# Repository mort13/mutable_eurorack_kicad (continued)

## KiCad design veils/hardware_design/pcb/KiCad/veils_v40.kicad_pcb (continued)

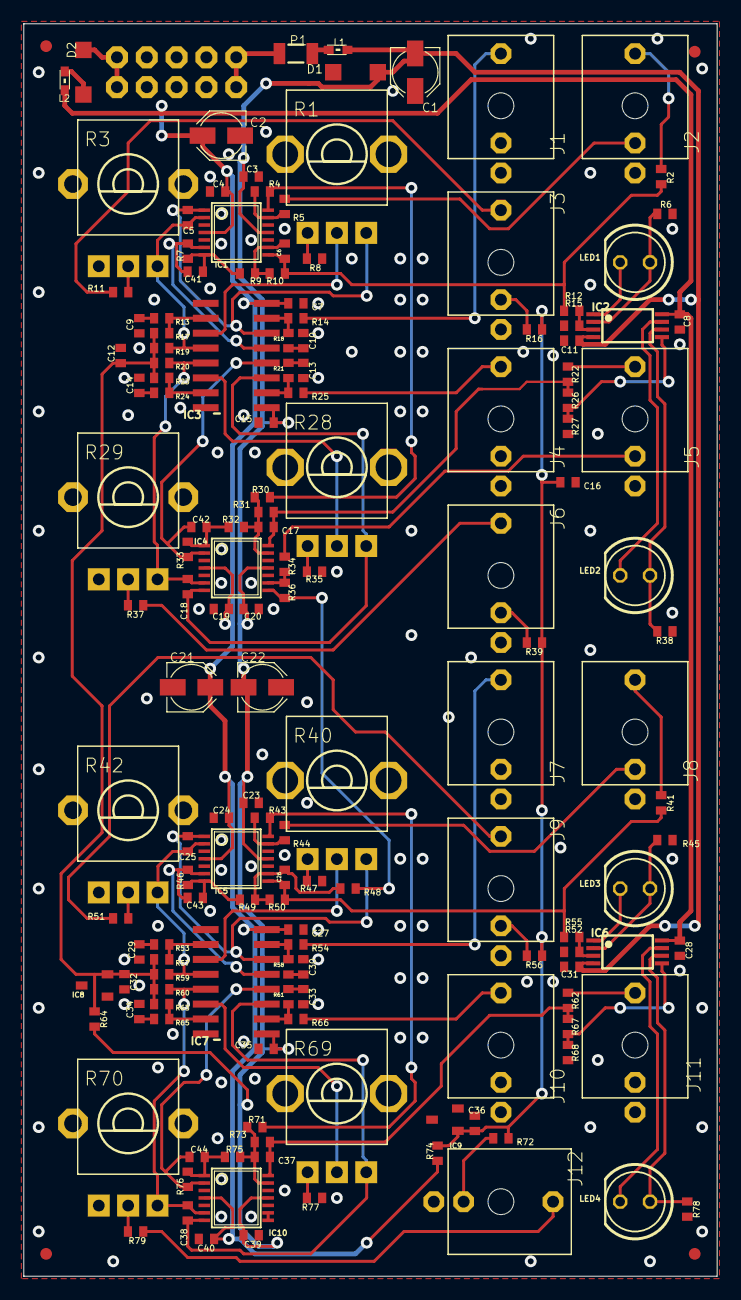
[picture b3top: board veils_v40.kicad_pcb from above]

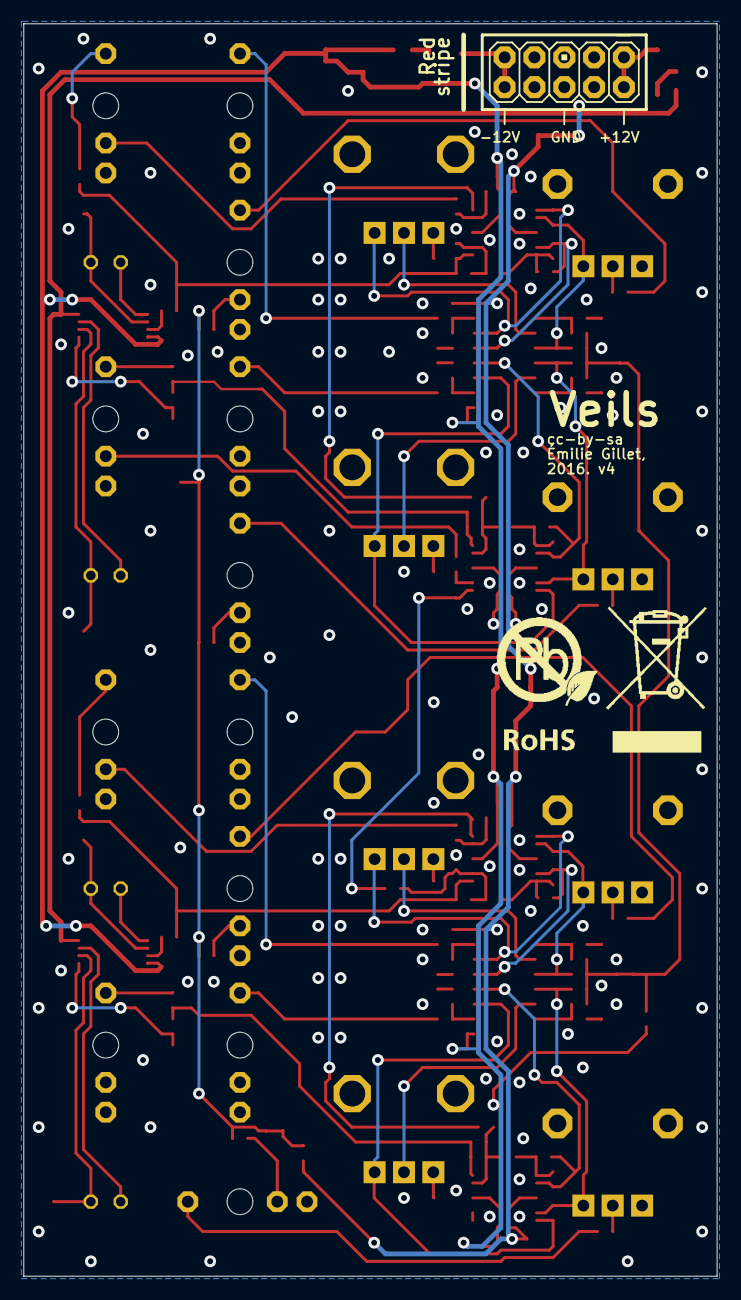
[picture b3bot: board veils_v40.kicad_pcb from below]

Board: 2 copper layers, 59.1 x 106.7 mm, 160 parts (2 on the bottom side), 99 nets.

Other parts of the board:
U$2: ROHS_BIG

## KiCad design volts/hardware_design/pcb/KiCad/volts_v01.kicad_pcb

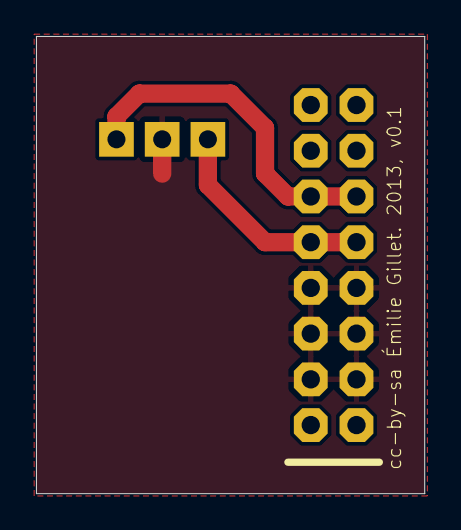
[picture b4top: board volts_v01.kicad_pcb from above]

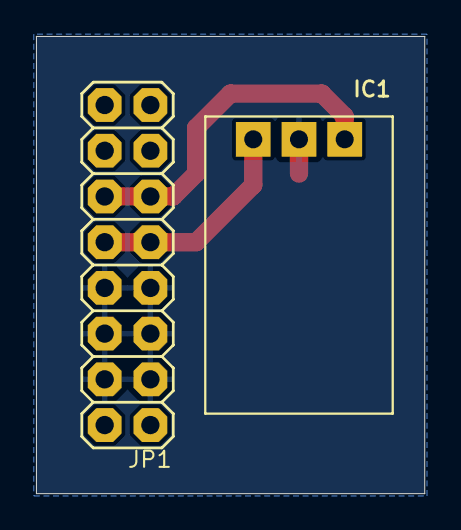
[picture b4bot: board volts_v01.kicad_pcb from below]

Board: 2 copper layers, 21.6 x 25.4 mm, 4 parts (2 on the bottom side), 3 nets.

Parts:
IC1: OKI-78SR-5/1.5-W36-C; OKI78SR
JP1: M08X2; 2X8
U$1: LOGO_5VOLTS
U$2: LOGO_5VOLTS_EDIT

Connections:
GND: IC1.2, JP1.9, JP1.10, JP1.11, JP1.12, JP1.13, JP1.14
unnamed: IC1.1, JP1.7, JP1.8
unnamed: IC1.3, JP1.5, JP1.6

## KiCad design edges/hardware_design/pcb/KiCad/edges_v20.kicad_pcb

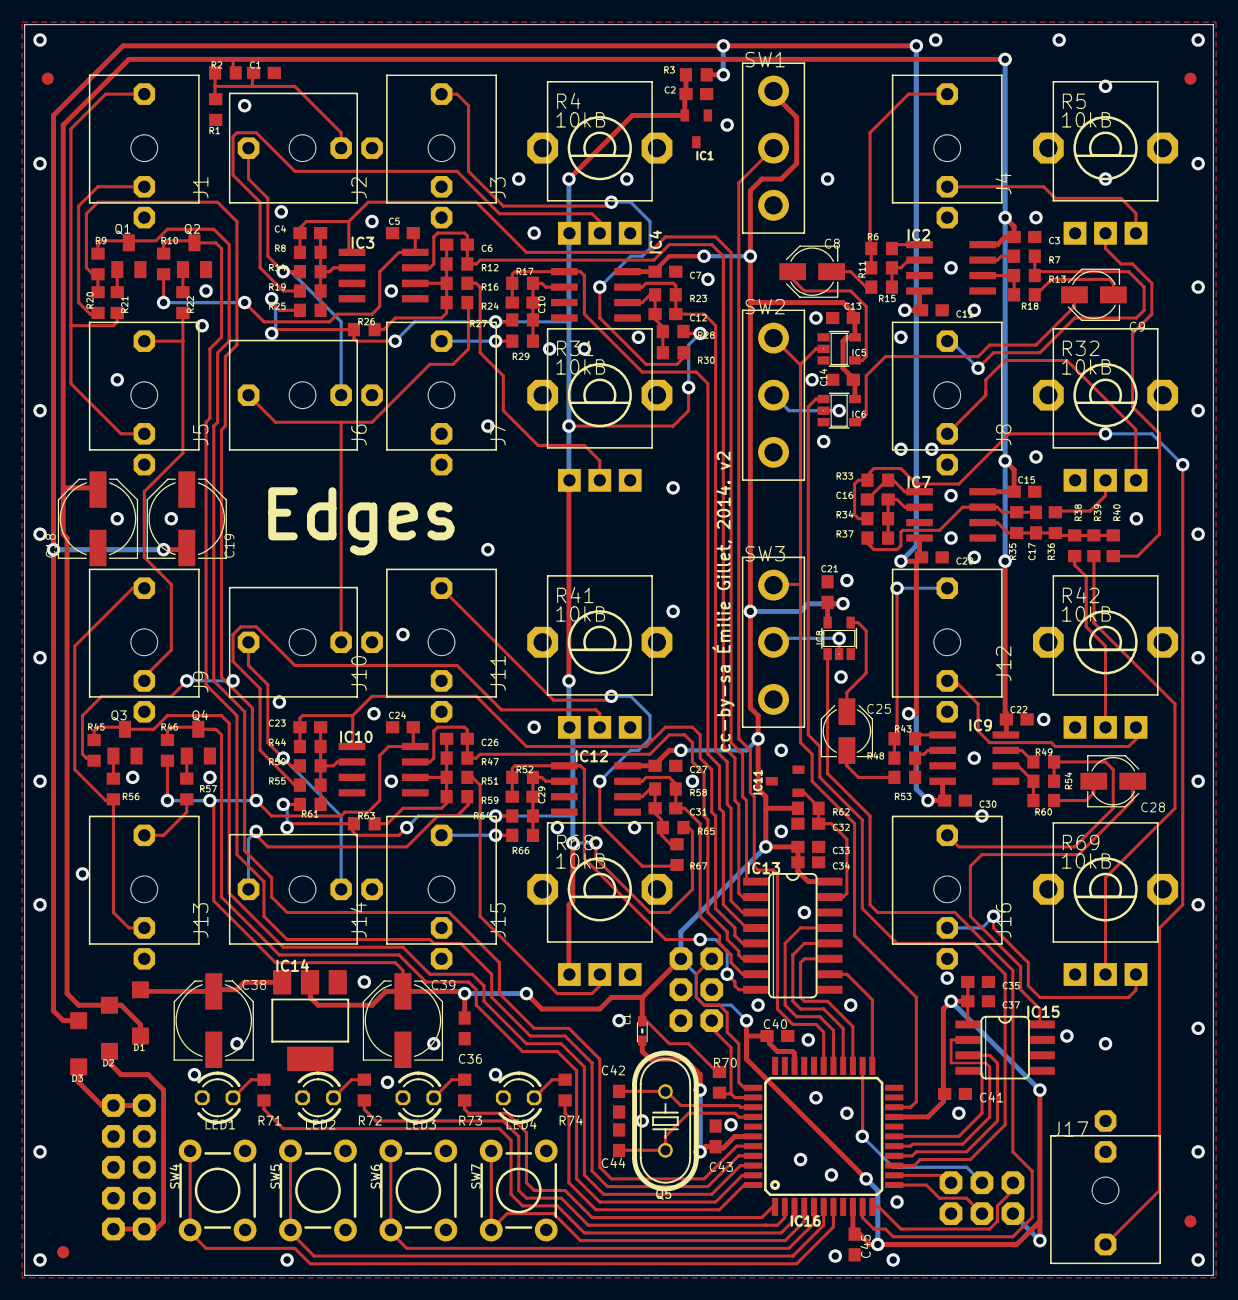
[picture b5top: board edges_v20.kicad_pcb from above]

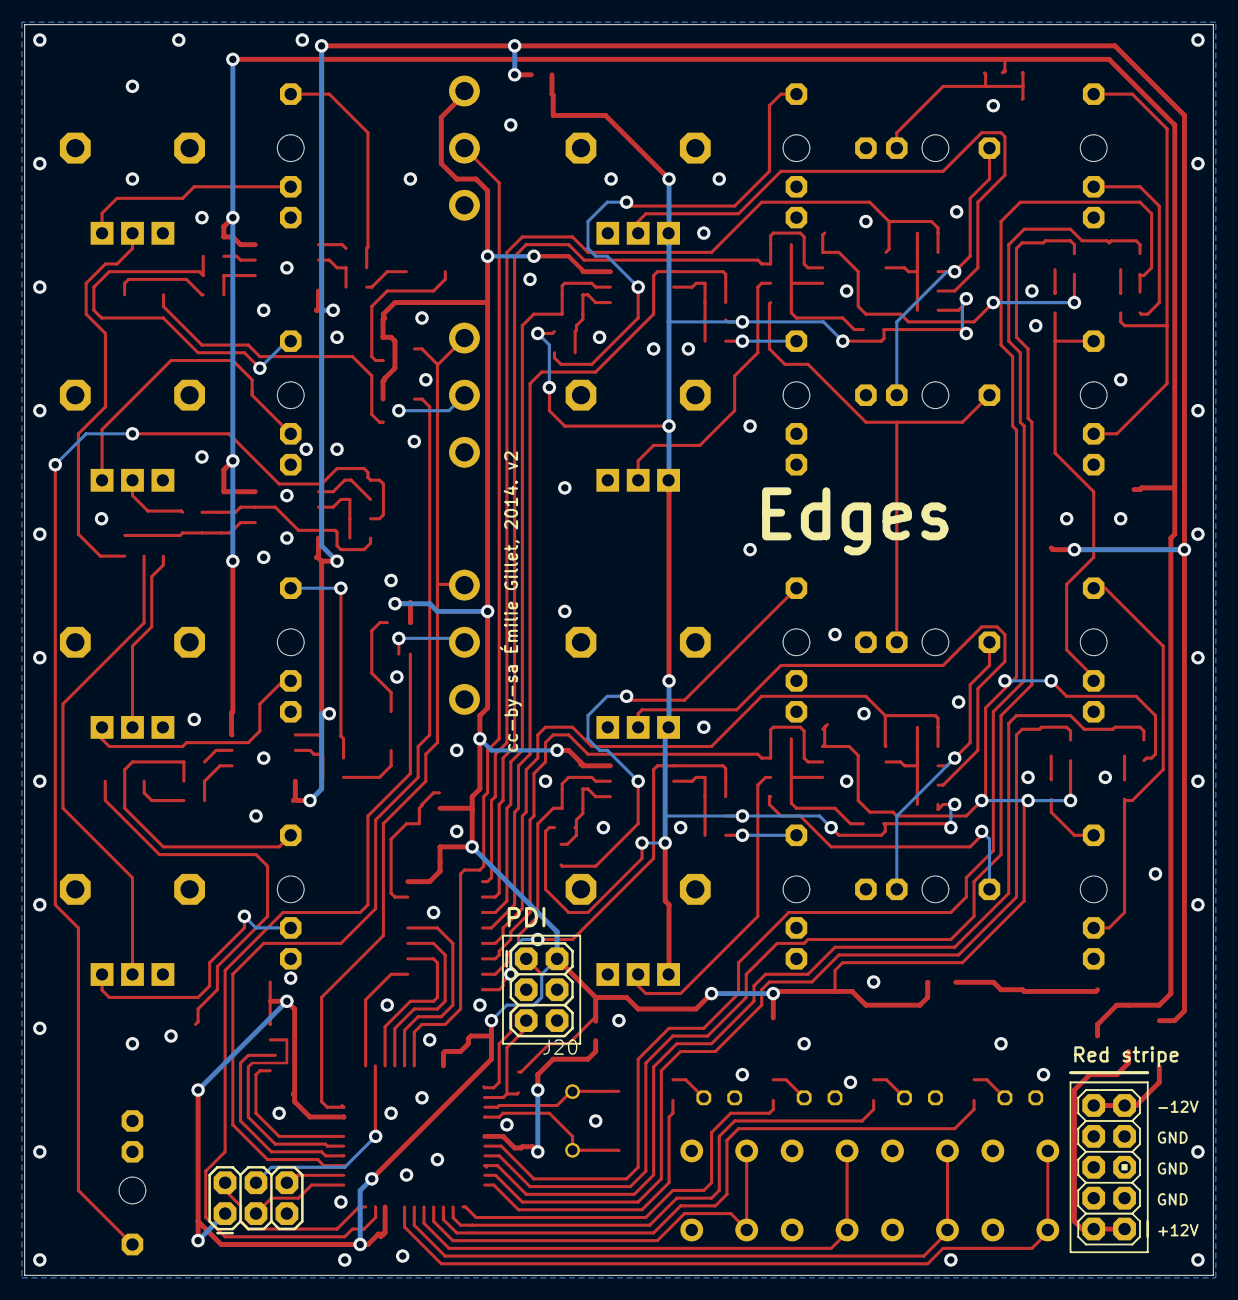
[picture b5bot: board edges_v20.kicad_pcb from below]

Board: 2 copper layers, 97.8 x 102.9 mm, 179 parts (3 on the bottom side), 118 nets.

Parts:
C1, C2, C32: 470n; C0603
C3, C5, C7, C11, C13, C14, C15, C20, C21, C22, C24, C27, C30, C34, C36, C37, C40, C41, C43, C45: 100n; C0603
C4, C6, C10, C12, C23, C26, C29, C31: 100p; C0603
C8, C9, C25, C28: 10u; PANASONIC_B
C16, C17, C42, C44: 18p; C0603
C18, C19, C38, C39: 47u; PANASONIC_D
C33, C35: 1u; C0603
D1, D2, D3: 1N5819HW; SOD123
IC1: LM4040 10V; DBZ_R-PDSO-G3
IC2, IC7, IC9: TL072D; SO08
IC3, IC4, IC10, IC12: MCP6002; SO08
IC5: 74AHC1G125DBV; SOT23-5
IC6, IC8: 74AHC1G86DBV; SOT23-5
IC11: LM4040B25; DBZ_R-PDSO-G3
IC13: MCP3208; SO16
IC14: LM1117-3.3; SOT223
IC15: MCP4822; SO08
IC16: ATXMEGA32A4U-AU; TQFP44
J1, J2, J3, J4, J5, J6, J7, J8, J9, J10, J11, J12, J13, J14, J15, J16, J17: PJ301_THONKICONN6; WQP_PJ_301M6
J18, J20: 2X3
J19: M05X2PTH; AVR_ICSP
JP1, JP2, JP3, JP4: FIDUCIAL1X2; FIDUCIAL-1X2
L1: 0603
LED1, LED2, LED3, LED4: LED3MM
Q1, Q2, Q3, Q4: MMBT3904; SOT23-BEC
Q5: 8MHz; HC49U70
R1: 2k; R0603
R2, R9, R10, R15, R18, R45, R46, R53, R60: 10k; R0603
R3: 300; R0603
R4, R5, R31, R32, R41, R42, R68, R69: 10kB; ALPS_POT_VERTICAL_PS
R6, R7, R20, R33, R43, R49, R62: 1k; R0603
R8, R12, R17, R23, R44, R47, R52, R58: 24.9k; R0603
R11, R13, R35, R48: 33k; R0603
R14, R21, R22, R24, R29, R30, R34, R36, R37, R38, R40, R50, R56, R57, R59, R66, R67: 100k; R0603
R16, R19, R25, R26, R27, R28, R51, R55, R61, R63, R64, R65: 200k; R0603
R39, R70: 39k; R0603
R54: 82k; R0603
R71, R72, R73, R74: 100; R0603
SW1, SW2, SW3: ES_100SP1T6B11M2QEH_SMALL
SW4, SW5, SW6, SW7: TACTILE-PTH

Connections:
+3V3: C5.1, C7.1, C13.1, C14.1, C21.1, C24.1, C27.1, C33.1, C34.1, C35.1, C36.1, C37.1, C39.+, C40.1, C41.1, C45.1, IC3.8, IC4.8, IC5.5, IC6.5, IC8.5, IC10.8, IC12.8, IC13.16, IC14.2, IC15.1, IC16.9, IC16.19, IC16.31, J18.1, J20.2, L1.1, R9.2, R10.2, R20.1, R45.2, R46.2, R62.1, R70.2, SW1.O
ADC_MISO: IC13.12, IC16.26
ADC_MOSI: IC13.11, IC16.25
ADC_SCK: IC13.13, IC16.27
ADC_SS: IC13.10, IC16.23
AREF: C32.1, IC11.1, IC13.15, R62.2
AREF_-10: C2.1, IC1.2, R3.2, R4.P$3, R25.1, R26.1, R27.1, R28.1, R31.P$3, R41.P$3, R61.1, R63.1, R64.1, R65.1, R68.P$3
CH1: C4.2, IC3.1, IC13.1, R8.2
CH2: C6.2, IC3.7, IC13.2, R12.2
CH3: C23.2, IC10.1, IC13.5, R44.2
CH4: C26.2, IC10.7, IC13.6, R47.2
CH5: C12.2, IC4.7, IC13.3, R23.2
CH6: C10.2, IC4.1, IC13.4, R17.2
CH7: C31.2, IC12.7, IC13.7, R58.2
CH8: C29.2, IC12.1, IC13.8, R52.2
CHANNEL1: C8.+, IC5.4
CHANNEL1_BUFFERED: J4.P3, R6.2, R11.2
CHANNEL1_RETURN: R5.P$2, R40.1
CHANNEL2: C9.+, IC6.4
CHANNEL2_BUFFERED: J8.P3, R7.2, R13.2
CHANNEL2_RETURN: R32.P$2, R36.1
CHANNEL3: C25.+, IC8.4
CHANNEL3_BUFFERED: J12.P3, R43.2, R48.2
CHANNEL3_RETURN: R38.1, R42.P$2
CHANNEL4: C28.+, IC15.8
CHANNEL4_BUFFERED: J16.P3, R49.2, R54.2
CHANNEL4_RETURN: R39.1, R69.P$2
COARSE1: R4.P$2, R19.1
COARSE2: R16.1, R31.P$2
COARSE3: R41.P$2, R55.1
COARSE4: R51.1, R68.P$2
CV1: J2.P3, J6.P2, R14.1
CV2: J6.P3, J10.P2, R24.1
CV3: J10.P3, J14.P2, R50.1
CV4: J14.P3, R59.1
DAC_MOSI: IC15.4, IC16.17
DAC_SCK: IC15.3, IC16.15
DAC_SS: IC15.2, IC16.16
FM1: J3.P3, R30.1
FM2: J7.P3, R29.1
FM3: J11.P3, R67.1
FM4: J15.P3, R66.1
GATE1: IC16.40, Q1.C, R9.1
GATE1_IN: J1.P3, J5.P2, R21.2
GATE1_LED: LED4.A, R74.2
GATE2: IC16.41, Q2.C, R10.1
GATE2_IN: J5.P3, J9.P2, R22.2
GATE2_LED: LED3.A, R73.2
GATE3: IC16.42, Q3.C, R45.1
GATE3_IN: J9.P3, J13.P2, R56.2
GATE3_LED: LED2.A, R72.2
GATE4: IC16.43, Q4.C, R46.1
GATE4_IN: J13.P3, R57.2
GATE4_LED: LED1.A, R71.2
GND: C1.2, C2.2, C3.2, C5.2, C7.2, C11.1, C13.2, C14.2, C15.2, C18.-, C19.+, C20.1, C21.2, C22.2, C24.2, C27.2, C30.1, C32.2, C33.2, C34.2, C35.2, C36.2, C37.2, C38.-, C39.-, C40.2, C41.2, C42.1, C43.2, C44.1, C45.2, IC1.1, IC2.3, IC2.5, IC3.3, IC3.4, IC3.5, IC4.3, IC4.4, IC4.5, IC5.1, IC5.3, IC6.3, IC7.3, IC7.5, IC8.3, IC9.3, IC9.5, IC10.3, IC10.4, IC10.5, IC11.2, IC12.3, IC12.4, IC12.5, IC13.9, IC13.14, IC14.1, IC15.5, IC15.7, IC16.8, IC16.18, IC16.30, IC16.38, J1.P1, J2.P1, J3.P1, J4.P1, J5.P1, J6.P1, J7.P1, J8.P1, J9.P1, J10.P1, J11.P1, J12.P1, J13.P1, J14.P1, J15.P1, J16.P1, J17.P1, J18.5, J19.3, J19.4, J19.5, J19.6, J19.7, J19.8, J20.6, LED1.K, LED2.K, LED3.K, LED4.K, Q1.E, Q2.E, Q3.E, Q4.E, R1.1, R4.P$1, R5.P$3, R31.P$1, R32.P$3, R41.P$1, R42.P$3, R68.P$1, R69.P$3, SW1.S, SW2.O, SW3.O, SW4.3, SW4.4, SW5.3, SW5.4, SW6.3, SW6.4, SW7.3, SW7.4
MIDI_IN: IC16.12, J18.3
MIX: J17.P3, R33.2, R34.2
unnamed: Q1.B, R21.1
unnamed: Q2.B, R22.1
unnamed: Q3.B, R56.1
unnamed: J8.P2, R32.P$1
unnamed: IC16.44, R74.1
unnamed: IC16.1, R73.1
unnamed: IC16.2, R72.1
unnamed: IC16.3, R71.1
unnamed: C23.1, IC10.2, R44.1, R50.2, R55.2, R61.2
unnamed: C10.1, IC4.2, R17.1, R27.2, R29.2
unnamed: J1.P2, R20.2
unnamed: C26.1, IC10.6, R47.1, R51.2, R59.2, R63.2
unnamed: C31.1, IC12.6, R58.1, R65.2, R67.2
unnamed: C29.1, IC12.2, R52.1, R64.2, R66.2
unnamed: IC6.1, IC16.14
unnamed: C8.-, R15.1
unnamed: IC8.2, SW3.P
unnamed: IC2.2, R11.1, R15.2
unnamed: IC2.1, R6.1
unnamed: IC6.2, SW2.P
unnamed: C9.-, R18.1
unnamed: IC2.6, R13.1, R18.2
unnamed: IC2.7, R7.1
unnamed: C25.-, R53.1
unnamed: C12.1, IC4.6, R23.1, R28.2, R30.2
unnamed: IC9.2, R48.1, R53.2
unnamed: IC9.1, R43.1
unnamed: C28.-, R60.1
unnamed: IC9.6, R54.1, R60.2
unnamed: IC9.7, R49.1
unnamed: C17.1, IC7.6, R35.1, R36.2, R38.2, R39.2, R40.2
unnamed: C16.1, IC7.2, R34.1, R37.2
unnamed: C16.2, IC7.1, R33.1
unnamed: C38.+, D1.C, IC14.3
unnamed: C43.1, IC16.39, L1.2
unnamed: J4.P2, R5.P$1
unnamed: IC8.1, IC16.10
unnamed: C17.2, IC7.7, R35.2, R37.1
unnamed: J12.P2, R42.P$1
unnamed: J16.P2, R69.P$1
unnamed: C6.1, IC3.6, R12.1, R16.2, R24.2, R26.2
unnamed: C1.1, J2.P2, R1.2, R2.1
unnamed: D2.A, J19.1, J19.2
unnamed: IC5.2, IC16.20, SW2.S, SW3.S
unnamed: D3.C, J19.9, J19.10
unnamed: C4.1, IC3.2, R8.1, R14.2, R19.2, R25.2
unnamed: C44.2, IC16.37, Q5.1
unnamed: C42.2, IC16.36, Q5.2
unnamed: Q4.B, R57.1
NES_TRIANGLE_CLK: IC16.24, J18.4
PDICLK: IC16.35, J20.5, R70.1
PDIDATA: IC16.34, J20.1
SW1: IC16.4, SW7.1, SW7.2
SW2: IC16.5, SW6.1, SW6.2
SW3: IC16.6, SW5.1, SW5.2
SW4: IC16.7, SW4.1, SW4.2
SW_MIDI_LEARN: IC16.11, J18.2
SW_MIDI_MODE: IC16.13, J18.6
SYNC_SWITCH: IC16.28, SW1.P
VCC: C3.1, C15.1, C18.+, C22.1, D1.A, D2.C, IC2.8, IC7.8, IC9.8, R2.2
VEE: C11.2, C19.-, C20.2, C30.2, D3.A, IC2.4, IC7.4, IC9.4, R3.1

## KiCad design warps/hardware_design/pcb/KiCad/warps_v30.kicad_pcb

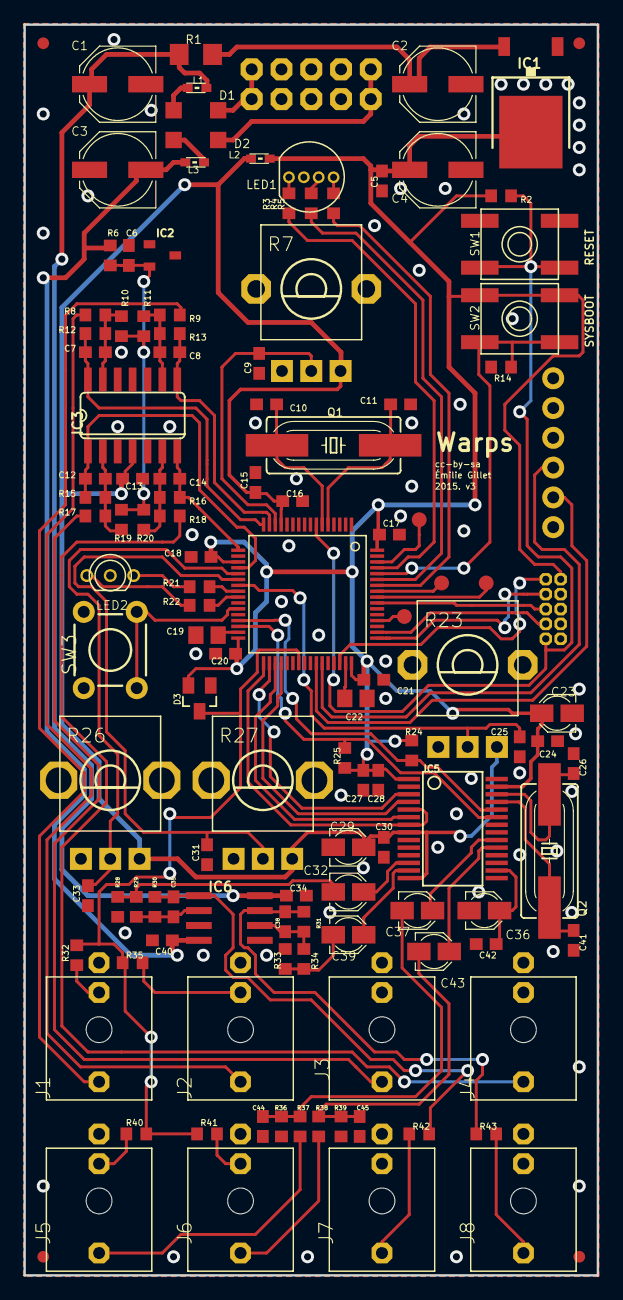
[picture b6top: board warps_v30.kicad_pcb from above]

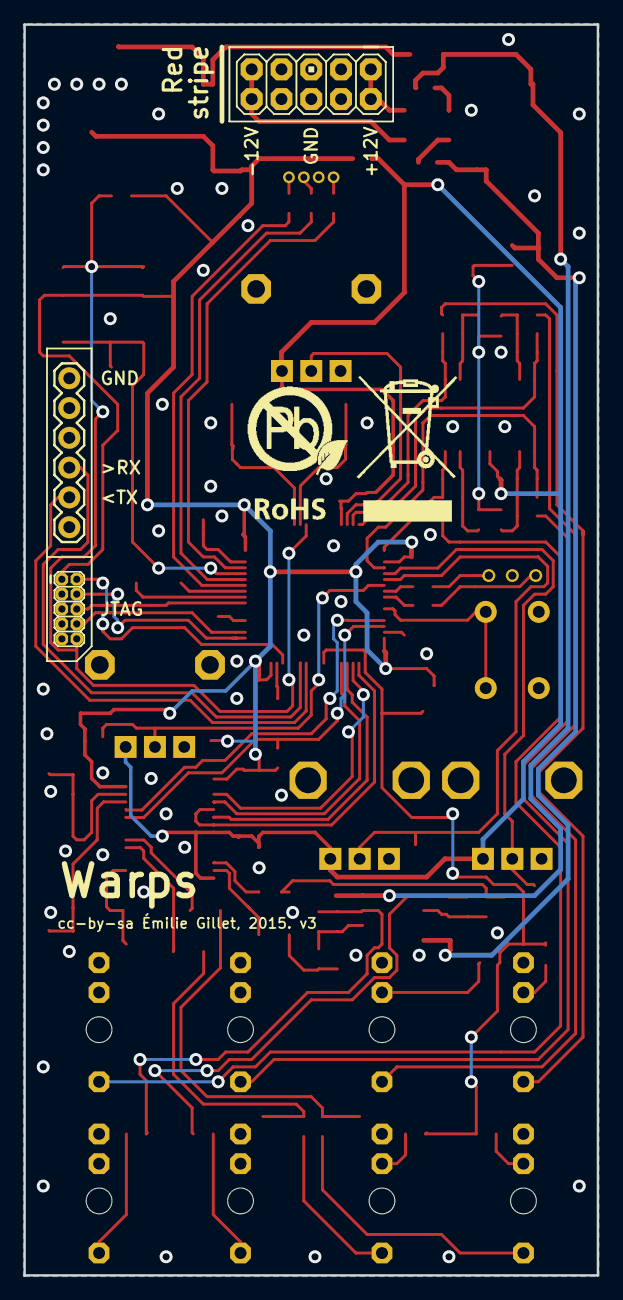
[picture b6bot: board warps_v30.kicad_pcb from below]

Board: 2 copper layers, 48.9 x 106.7 mm, 127 parts (4 on the bottom side), 84 nets.

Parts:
C1, C2, C3, C4: 47u; PANASONIC_D
C5, C6, C9, C13, C16, C17, C18, C20, C21, C24, C25, C28, C30, C31, C33, C34, C40, C42: 100n; C0603
C7, C8, C12, C14: 4.7n; C0603
C10, C11, C26, C35, C38, C41: 18p; C0603
C15, C27: 1u; C0603
C19, C22: 2.2u; C0805
C23, C29, C32, C36, C37, C39, C43: 10u; PANASONIC_A
C44, C45: 220p; C0603
D1, D2: 1N5819HW; SOD123
D3: BAT54S; SOT23
F1, F2, F3, F4: FIDUCIAL1X2; FIDUCIAL-1X2
IC1: LM1117-3.3; TO252
IC2: LM4040B10; DBZ_R-PDSO-G3
IC3: MCP6004; SO14
IC4: STM32F405RGT6; TQFP-10X10-64
IC5: WM8731; SSOP28
IC6: TL072; SO08
J1, J2, J3, J4, J5, J6, J7, J8: PJ301_THONKICONN6; WQP_PJ_301M6
JP1: M05X2MINIJTAG; 2X5-1.27
JP2: 1X06
JP3: M05X2PTH; AVR_ICSP
L1, L2, L3: 0603
LED1: WP154A4SUREQBFZG; LED-TRICOLOR-THROUGHHOLE
LED2: WP115VEGW; LED-BICOLOR-THROUGHHOLE
Q1: 8MHz; HC49UP
Q2: 12.288MHz; HC49UP
R1: 4.7; R1206
R2, R14: 10k; R0603
R3, R4, R5: 100; R0603
R6: 4.7k; R0603
R7, R23: 10kB; ALPS_POT_VERTICAL_PS
R8, R9, R17, R18: 100k; R0603
R10, R11: 120k; R0603
R12, R13, R37, R38: 36k; R0603
R15, R16: 33k; R0603
R19, R20, R32, R35: 200k; R0603
R21, R22: 180; R0603
R24, R25: 2.2k; R0603
R26, R27: 10kB; ALPS_POT_VERTICAL
R28, R30, R31, R33: 47k; R0603
R29, R34, R36, R39: 6.8k; R0603
R40, R41: DNP; R0603
R42, R43: 1.0k; R0603
SW1, SW2: EVQ-Q2
SW3: TACTILE-PTH
TP1, TP2, TP3, TP4: TEST-POINT3X5; PAD.03X.05
U$2: ROHS_BIG

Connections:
+3V3: C4.+, C5.1, C17.1, C18.1, C20.1, C21.1, C23.+, C24.1, C27.1, C28.1, D3.2, IC1.3, IC4.19, IC4.32, IC4.48, IC4.64, IC5.1, IC5.27, JP1.1, L2.1, R2.2, R24.2, R25.2, SW2.B, SW2.B'
+3V3_A: C13.1, C15.1, C16.1, C29.+, C30.1, IC3.4, IC4.13, IC5.8, IC5.14, L2.2, R7.P$1, R23.P$1, R26.P$1, R27.P$1
ALGORITHM_CV: C12.2, IC3.1, IC4.20, R15.1
ALGORITHM_POT: C9.1, IC4.14, R7.P$2
AREF_-10: C6.1, IC2.2, R6.2, R10.2, R11.2, R19.2, R20.2
AUX_OUT: C39.+, IC5.13
BOOT_FLASH: IC4.60, R14.2, SW2.A, SW2.A'
GND: C1.-, C2.-, C3.+, C4.-, C5.2, C6.2, C9.2, C10.1, C11.1, C13.2, C15.2, C16.2, C17.2, C18.2, C19.2, C20.2, C21.2, C22.2, C23.-, C24.2, C25.2, C26.1, C27.2, C28.2, C29.-, C30.2, C31.2, C33.2, C34.2, C36.-, C40.1, C41.1, C42.2, C44.2, C45.2, D3.1, IC1.1, IC2.1, IC3.3, IC3.5, IC3.10, IC3.11, IC3.12, IC4.12, IC4.18, IC4.26, IC4.28, IC4.63, IC5.11, IC5.15, IC5.21, IC5.22, IC5.28, IC6.3, IC6.5, J1.P1, J2.P1, J3.P1, J4.P1, J5.P1, J6.P1, J7.P1, J8.P1, JP1.3, JP1.5, JP1.9, JP2.1, JP3.3, JP3.4, JP3.5, JP3.6, JP3.7, JP3.8, LED1.GND, LED2.2, R7.P$3, R14.1, R23.P$3, R26.P$3, R27.P$3, R28.1, R33.1, R36.1, R39.1, SW1.A, SW1.A', SW3.1, SW3.2
I2C_SCL: IC4.29, IC5.24, R24.1
I2C_SDA: IC4.30, IC5.23, R25.1
I2S_LRCK: IC4.33, IC5.5, IC5.7
I2S_SCK: IC4.34, IC5.3
I2S_SIN: IC4.35, IC5.6
I2S_SOUT: IC4.36, IC5.4
IN_1: C37.+, IC5.20
IN_2: C43.+, IC5.19
JTCK: IC4.49, JP1.4
JTDI: IC4.50, JP1.8
JTDO: IC4.55, JP1.6
JTMS: IC4.46, JP1.2
LED_B: IC4.59, R4.1
LED_CARRIER_G: IC4.25, R22.1
LED_CARRIER_R: IC4.24, R21.1
LED_G: IC4.58, R5.1
LED_R: IC4.61, R3.1
LEVEL_1_CV: C8.2, IC3.8, IC4.15, R13.1
LEVEL_1_POT: C33.1, IC4.21, R26.P$2
LEVEL_2_CV: C7.2, IC3.14, IC4.16, R12.1
LEVEL_2_POT: C31.1, IC4.22, R27.P$2
MOD_OUT: C32.+, IC5.12
unnamed: J1.P3, R9.2
unnamed: C8.1, IC3.9, R9.1, R11.1, R13.2
unnamed: LED2.3, R21.2
unnamed: J2.P3, R8.2
unnamed: C7.1, IC3.13, R8.1, R10.1, R12.2
unnamed: J4.P3, R18.2
unnamed: C11.2, IC4.5, Q1.2
unnamed: C10.2, IC4.6, Q1.1
unnamed: J1.P2, R32.2
unnamed: J3.P3, R17.2
unnamed: C12.1, IC3.2, R15.2, R17.1, R19.1
unnamed: J2.P2, R35.2
unnamed: C22.1, IC4.47
unnamed: LED2.1, R22.2
unnamed: C14.1, IC3.6, R16.2, R18.1, R20.1
unnamed: C2.+, IC1.2, R1.1
unnamed: C36.+, C42.1, IC5.16
unnamed: C37.-, C44.1, R36.2, R37.1
unnamed: C19.1, IC4.31
unnamed: J6.P3, R38.2
unnamed: J5.P3, R37.2
unnamed: C43.-, C45.1, R38.1, R39.2
unnamed: C39.-, R33.2, R34.2
unnamed: IC4.56, TP3.P$1
unnamed: C38.1, IC6.6, R31.2, R34.1
unnamed: IC4.57, TP2.P$1
unnamed: IC4.52, TP4.P$1
unnamed: C38.2, IC6.7, R31.1, R43.2
unnamed: J8.P3, R43.1
unnamed: IC4.62, TP1.P$1
unnamed: C32.-, R28.2, R29.2
unnamed: C35.1, IC6.2, R29.1, R30.2
unnamed: C35.2, IC6.1, R30.1, R42.2
unnamed: J7.P3, R42.1
unnamed: LED1.RED, R3.2
unnamed: LED1.BLU, R4.2
unnamed: LED1.GRN, R5.2
unnamed: J6.P2, R41.1
unnamed: J5.P2, R40.1
unnamed: C41.2, IC5.25, Q2.2
unnamed: C26.2, IC5.26, Q2.1
unnamed: D1.C, L1.2
unnamed: D2.A, L3.2
unnamed: D1.A, JP3.1, JP3.2
unnamed: D2.C, JP3.9, JP3.10
NORMALIZATION_PROBE: D3.3, IC4.39, R32.1, R35.1, R40.2, R41.2
PARAMETER_CV: C14.2, IC3.7, IC4.17, R16.1
PARAMETER_POT: C25.1, IC4.23, R23.P$2
RESET: IC4.7, JP1.10, R2.1, SW1.B, SW1.B'
RX: IC4.43, JP2.4
SW_CARRIER: IC4.27, SW3.3, SW3.4
TX: IC4.42, JP2.5
VCC: C1.+, C34.1, IC6.8, L1.1, R1.2
VEE: C3.-, C40.2, IC6.4, L3.1, R6.1

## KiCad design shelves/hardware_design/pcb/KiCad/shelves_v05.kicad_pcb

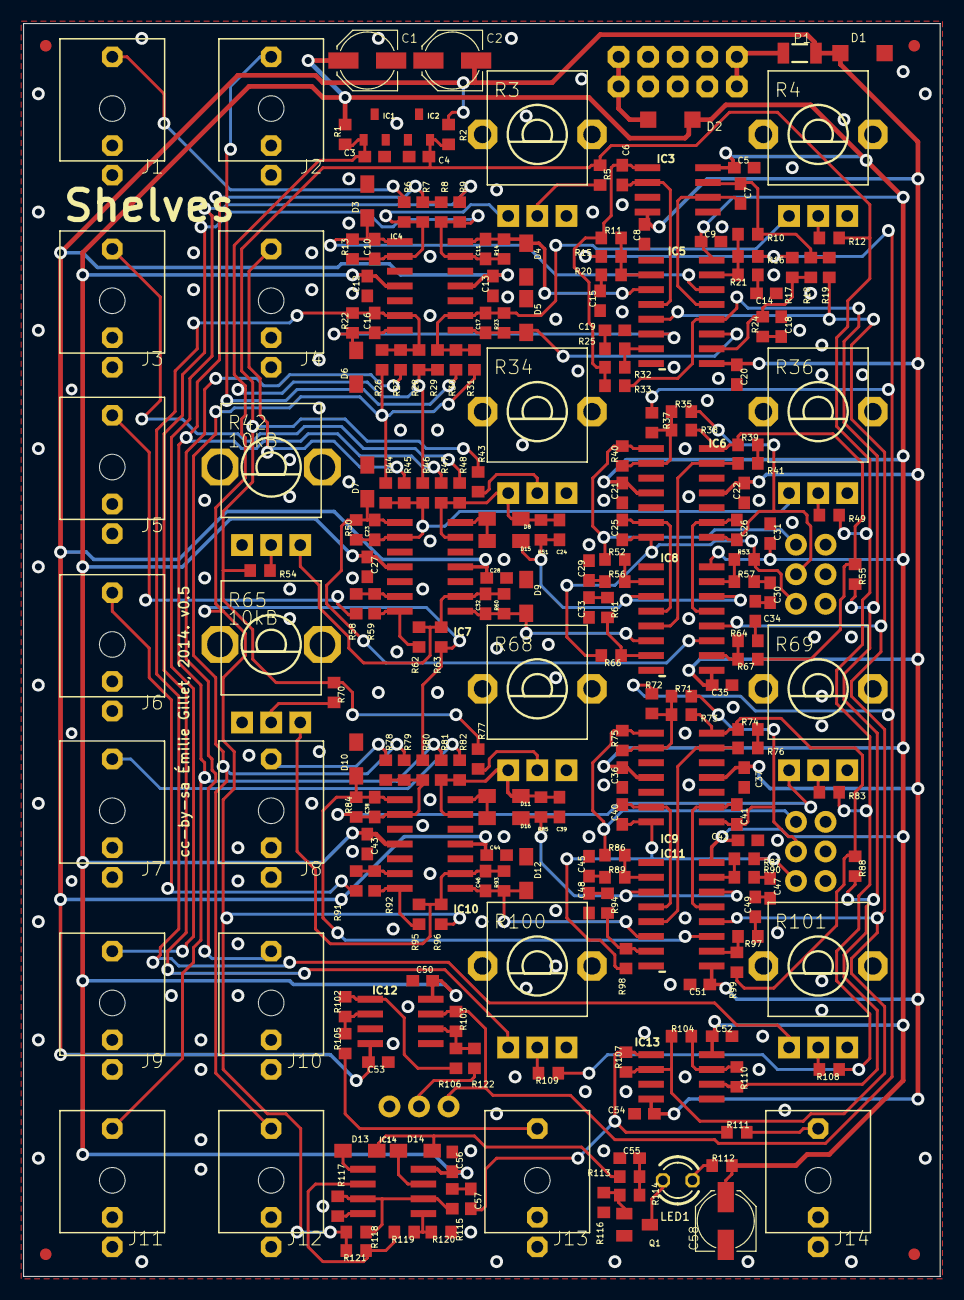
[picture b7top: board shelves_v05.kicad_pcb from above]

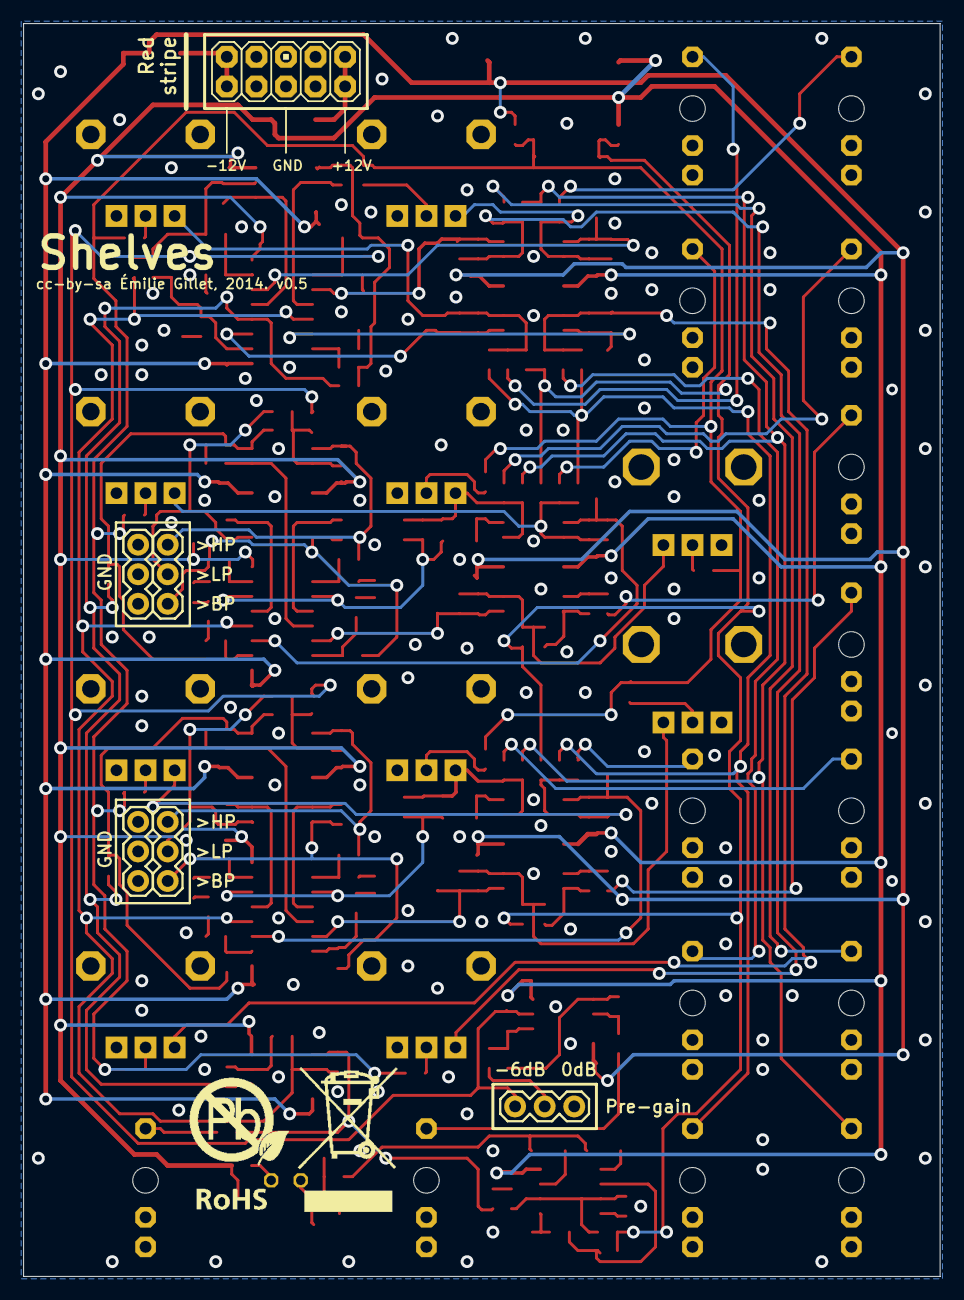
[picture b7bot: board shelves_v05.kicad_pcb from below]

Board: 2 copper layers, 78.7 x 107.6 mm, 238 parts (7 on the bottom side), 123 nets.

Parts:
C1, C2, C58: 22u; PANASONIC_C
C3, C4, C5, C8, C9, C12, C13, C20, C21, C22, C27, C28, C31, C35, C36, C37, C42, C43, C44, C50, C51, C52, C53, C54, C55, C56, C57: 100n; C0603
C6, C7, C25, C26, C40, C41: 68p; C0603
C10, C11, C14, C15, C16, C17, C18, C19, C23, C24, C29, C30, C32, C33, C34, C38, C39, C45, C46, C47, C48, C49: 560p; C0603
D1, D2: 1N5819HW; SOD123
D3, D4, D5, D6, D7, D8, D9, D10, D11, D12, D13, D14, D15, D16: 1N4148; SOD323-W
IC1, IC2: LM4040B10; DBZ_R-PDSO-G3
IC3, IC12, IC13, IC14: TL072D; SO08
IC4, IC6, IC7, IC9, IC10: TL074D; SO14
IC5, IC8, IC11: V2164SZ; SOIC16N
J1, J2, J3, J4, J5, J6, J7, J8, J9, J10, J11, J12, J13, J14: PJ301_THONKICONN6; WQP_PJ_301M6
JP1, JP2, JP3, JP4: FIDUCIAL1X2; FIDUCIAL-1X2
JP5, JP6, JP7, JP12, JP13: 1X03
JP11: M05X2PTH; AVR_ICSP
LED1: WP-710A10GD; LED3MM
P1: PTCSMD; PTC-1206
Q1: MMBT3904; SOT23-BEC
R1: 3.3k; R0603
R2, R111, R112: 1.0k; R0603
R3, R4, R34, R36, R68, R69, R100, R101: 10kB; ALPS_POT_VERTICAL_PS
R5, R6, R7, R8, R9, R10, R11, R12, R15, R16, R17, R18, R19, R32, R33, R35, R37, R38, R39, R40, R41, R43, R47, R48, R49, R52, R53, R55, R58, R59, R66, R67, R71, R72, R73, R74, R75, R76, R77, R81, R82, R83, R86, R87, R88, R91, R92, R98, R99, R102, R103, R104, R105, R108, R109, R110, R114, R115, R117, R118, R120, R121, R122: 100k; R0603
R13, R14, R51, R85: 18k; R0603
R20, R21, R24, R25, R56, R57, R61, R64, R89, R90, R94, R97: 510; R0603
R22, R23, R50, R84, R113: 12k; R0603
R26, R27, R30, R31, R44, R45, R78, R79: 120k; R0603
R28, R29, R46, R54, R70, R80, R106, R107: 200k; R0603
R42, R65: 10kB; ALPS_POT_VERTICAL
R60, R93, R116: 22k; R0603
R62, R95: 150k; R0603
R63, R96: 1.5M; R0603
R119: 220k; R0603
U$2: ROHS_BIG

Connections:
AREF_+10: C3.1, IC1.1, R1.2, R28.1, R29.1, R46.1, R63.1, R80.1, R96.1, R118.2, R121.2
AREF_-10: C4.1, IC2.2, R2.2, R5.1, R12.1, R43.1, R49.1, R54.1, R70.1, R77.1, R83.1, R108.1, R109.1
BP_1: C40.2, IC9.7, JP13.1, R87.1, R98.1
BP_2: C25.2, IC6.7, JP5.1, R53.1, R66.1
F_GLOBAL: J11.P3, R7.1, R8.1, R47.1, R81.1
GAIN_GLOBAL: J12.P3, R26.1, R31.1, R44.1, R79.1
GND: C1.-, C2.+, C3.2, C4.2, C5.2, C8.1, C9.2, C12.2, C13.1, C14.2, C15.2, C18.2, C19.2, C20.1, C21.2, C22.1, C27.2, C28.1, C29.2, C30.2, C31.2, C33.2, C34.2, C35.1, C36.2, C37.1, C42.2, C43.2, C44.1, C45.2, C47.2, C48.2, C49.2, C50.2, C51.1, C52.2, C53.1, C54.1, C55.2, C56.2, C58.-, D1.C, D3.A, D4.A, D5.A, D6.A, D7.A, D9.A, D10.A, D12.A, IC1.2, IC2.1, IC3.3, IC3.5, IC4.3, IC4.5, IC4.10, IC4.12, IC5.8, IC6.3, IC6.5, IC6.10, IC6.12, IC7.3, IC7.5, IC7.10, IC7.12, IC8.8, IC9.3, IC9.5, IC9.10, IC9.12, IC10.3, IC10.5, IC10.10, IC10.12, IC11.8, IC12.3, IC12.5, IC13.3, IC13.5, IC14.4, J1.P1, J2.P1, J3.P1, J4.P1, J5.P1, J6.P1, J7.P1, J8.P1, J9.P1, J10.P1, J11.P1, J12.P1, J13.P1, J14.P1, JP6.1, JP6.2, JP6.3, JP7.1, JP7.2, JP7.3, JP11.3, JP11.4, JP11.5, JP11.6, JP11.7, JP11.8, Q1.E, R3.P$1, R4.P$1, R34.P$1, R36.P$1, R42.P$3, R65.P$3, R68.P$1, R69.P$1, R100.P$1, R101.P$1, R116.1, R117.1, R120.1
HP_1: IC9.1, JP13.3, R75.2, R86.1
HP_2: IC6.1, JP5.3, R40.2, R52.1
IN: IC12.7, JP12.3, R15.1, R16.1, R17.1, R37.1, R72.1, R103.2
IN_INV: IC12.1, R102.2, R106.1
IN_INV1: IC13.7, R104.1, R110.2
J_HF_CV: J2.P3, R30.1
J_HF_F: J1.P3, R6.1
J_IN: J13.P3, R105.1
J_LF_CV: J10.P3, R27.1
J_LF_F: J9.P3, R9.1
LP: C6.2, IC3.1, R11.2, R32.1, R33.1
LP1: C7.2, IC3.7, R10.2, R18.1, R19.1
MID1_F1: C24.1, D15.C, IC8.3, IC8.14, R51.2
MID1_F2: C39.1, D16.C, IC11.3, IC11.14, R85.2
MINUS_BUS: IC5.5, IC8.12, IC11.12, IC13.2, R19.2, R104.2, R107.1
unnamed: IC5.2, R11.1, R15.2, R20.2
unnamed: C19.1, R25.1
unnamed: C11.1, D4.C, IC4.14, IC5.3, R14.2
unnamed: C6.1, IC3.2, IC5.4
unnamed: C14.1, R21.1
unnamed: JP12.2, R122.2
unnamed: C16.1, D6.C, IC4.7, IC5.6, R22.2
unnamed: D11.C, D16.A, IC10.14
unnamed: IC12.2, R102.1, R105.2
unnamed: C15.1, R20.1
unnamed: IC10.7, R92.2, R95.1
unnamed: R100.P$2, R109.2
unnamed: C16.2, IC4.6, R22.1, R26.2, R27.2, R28.2, R101.P$3
unnamed: D8.C, D15.A, IC7.14
unnamed: R101.P$2, R108.2
unnamed: IC5.15, R10.1, R16.2, R21.2
unnamed: IC5.7, R25.2, R32.2
unnamed: C11.2, IC4.13, R8.2, R9.2, R14.1, R100.P$3
unnamed: C7.1, IC3.6, IC5.13
unnamed: R3.P$2, R5.2
unnamed: C17.1, D5.C, IC4.8, IC5.11, R23.2
unnamed: C17.2, IC4.9, R4.P$3, R23.1, R29.2, R30.2, R31.2
unnamed: C45.1, R89.1
unnamed: R4.P$2, R12.2
unnamed: C10.2, IC4.2, R3.P$3, R6.2, R7.2, R13.1
unnamed: C18.1, R24.1
unnamed: IC5.10, R17.2, R18.2, R24.2
unnamed: IC12.6, R103.1, R106.2, R122.1
unnamed: C10.1, D3.C, IC4.1, IC5.14, R13.2
unnamed: J7.P3, R82.1
unnamed: R68.P$2, R77.2
unnamed: C38.1, D10.C, IC10.1, IC11.11, R84.2
unnamed: C38.2, IC10.2, R69.P$3, R78.2, R79.2, R80.2, R84.1
unnamed: J8.P3, R78.1
unnamed: R69.P$2, R83.2
unnamed: C39.2, D11.A, IC10.13, R68.P$3, R81.2, R82.2, R85.1
unnamed: C49.1, R97.1
unnamed: IC11.10, R97.2, R99.2
unnamed: IC9.2, R71.1, R72.2, R73.1, R75.1
unnamed: IC11.2, R86.2, R89.2
unnamed: C40.1, IC9.6, IC11.4
unnamed: C47.1, R90.1
unnamed: C29.1, R56.1
unnamed: IC11.15, R87.2, R90.2
unnamed: C41.1, IC9.9, IC11.13
unnamed: C41.2, IC9.8, JP13.2, R71.2
unnamed: C48.1, R94.1
unnamed: IC11.7, R94.2, R98.2
unnamed: IC9.13, IC11.5, R76.2
unnamed: R74.2, R76.1
unnamed: IC9.14, R73.2, R74.1, R88.1, R99.1
unnamed: D2.A, JP11.1, JP11.2
unnamed: C46.1, D12.C, IC10.8, IC11.6, R93.2
unnamed: C46.2, IC10.9, R65.P$1, R93.1, R95.2, R96.2
unnamed: R65.P$2, R70.2
unnamed: LED1.K, Q1.C
unnamed: IC7.7, R59.2, R62.1
unnamed: J6.P3, R91.1
unnamed: J3.P3, R48.1
unnamed: JP11.9, JP11.10, P1.2
unnamed: R34.P$2, R43.2
unnamed: C23.1, D7.C, IC7.1, IC8.11, R50.2
unnamed: C23.2, IC7.2, R36.P$3, R44.2, R45.2, R46.2, R50.1
unnamed: J4.P3, R45.1
unnamed: R36.P$2, R49.2
unnamed: C24.2, D8.A, IC7.13, R34.P$3, R47.2, R48.2, R51.1
unnamed: C34.1, R64.1
unnamed: IC8.10, R64.2, R67.2
unnamed: IC6.2, R35.1, R37.2, R38.1, R40.1
unnamed: IC8.2, R52.2, R56.2
unnamed: C25.1, IC6.6, IC8.4
unnamed: C30.1, R57.1
unnamed: IC8.15, R53.2, R57.2
unnamed: C26.1, IC6.9, IC8.13
unnamed: C26.2, IC6.8, JP5.2, R35.2
unnamed: C33.1, R61.1
unnamed: IC8.7, R61.2, R66.2
unnamed: IC6.13, IC8.5, R41.2
unnamed: R39.2, R41.1
unnamed: IC6.14, R38.2, R39.1, R55.1, R67.1
unnamed: C32.1, D9.C, IC7.8, IC8.6, R60.2
unnamed: C32.2, IC7.9, R42.P$1, R60.1, R62.2, R63.2
unnamed: IC7.6, R58.2, R59.1
unnamed: R42.P$2, R54.2
unnamed: IC10.6, R91.2, R92.1
unnamed: J5.P3, R58.1
unnamed: J14.P3, R111.2
unnamed: C57.1, R115.1
unnamed: IC14.3, IC14.6, R115.2, R117.2, R118.1
unnamed: IC14.2, R119.2, R121.1
unnamed: C55.1, R113.2, R114.1
unnamed: IC14.5, R119.1, R120.2
unnamed: D13.A, IC14.1
unnamed: D14.A, IC14.7
unnamed: D13.C, D14.C, R113.1
unnamed: LED1.A, R112.1
unnamed: Q1.B, R114.2, R116.2
OUTPUT: C57.2, IC13.1, R107.2, R111.1
PLUS_BUS: IC5.12, IC13.6, R33.2, R55.2, R88.2, R110.1
VCC: C1.+, C5.1, C9.1, C12.1, C21.1, C27.1, C31.1, C36.1, C42.1, C43.1, C50.1, C52.1, C56.1, C58.+, D2.C, IC3.8, IC4.4, IC5.16, IC6.4, IC7.4, IC8.16, IC9.4, IC10.4, IC11.16, IC12.8, IC13.8, IC14.8, R1.1, R112.2
VEE: C2.-, C8.2, C13.2, C20.2, C22.2, C28.2, C35.2, C37.2, C44.2, C51.2, C53.2, C54.2, D1.A, IC3.4, IC4.11, IC5.9, IC6.11, IC7.11, IC8.9, IC9.11, IC10.11, IC11.9, IC12.4, IC13.4, P1.1, R2.1
